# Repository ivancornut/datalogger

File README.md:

# Open Ecophysio Dataloggers
A competitive datalogger for use in environmental science. It is well adapted for work in remote locations with little access to networks. 

The big version of the datalogger is made to run on 12 or 24V lead batteries. This version has options to switch 12V or 5V loads.

The small version can run on 3 or 4 AA NiMh cells. It is made in a way that ensures very low consumption during sleep (few µAs). This gurantees around a year of logging before needing a battery change. 

Both versions have:
- a micro-SD card slot
- a very low-drift RTC for precise time-keeping
- battery voltage monitoring
- polarity and over-current protection

The interfacing software is compatible with windows, macOS and linux computers. It is made to be as simple to use as possible.

  * [Hardware](#hardware)
    + [Full size datalogger](#full-size-datalogger)
    + [Micro sized datalogger](#micro-sized-datalogger)
  * [Software](#software)
    + [On the computer](#on-the-computer)
    + [On the datalogger](#on-the-datalogger)

## Hardware
### Full size datalogger

We use a custom made PCB that integrates
- A battery input (usable with 12V lead batteries)
- a low consumption and high efficiency step-down converter that can convert 6-40V down to 5V
- a low-drift RTC clock
- An SD card slot
- two controllable power outputs of 5V and 12V (or battery voltage) using MOSFETs
- temperature corrected reference frequency generators from the RTC chip
- Qwiic compatible I2C and UART connectors
- A way to measure input battery voltage
### Micro sized datalogger

This is a miniaturized version of the big pcb when size is a constraint. It pushed all the power and clock circuitry beneath the Pi Pico.
It lacks some functionality of the bigger version such as the controllable power outputs and the full shutdown circuitry. 

## Software
### On the computer

We use two GUIs on the computer:
- one that generates the json configuration file for the datalogger
- one that enables communication with the datalogger to update the clock and download files from the SD card

The datalogger management GUI also allows you to setup the datalogger with all the necessary libraries and config files to start datalogging right away.
#### Windows installation of the management GUI
The graphical user interface to perform some interfacing functions was made to be as easy to use as possible. For windows an executable file was created by using the pyinstaller library. 

To run on windows you first need to install python on your computer. You can install it easily from the windows store.
Then open up the powershell:
```
pip install mpremote
```
That should do the trick and you can just run the full_management_gui.exe in the Software/computer folder. 
#### Linux machine
You just need to install the mpremote tool. 
```
pip install mpremote
```
And then go to the folder containing full_management_gui.py: 
```
python full_management_gui.py
```

### On the datalogger
We use two modules. The datalogger module and the sensor module.

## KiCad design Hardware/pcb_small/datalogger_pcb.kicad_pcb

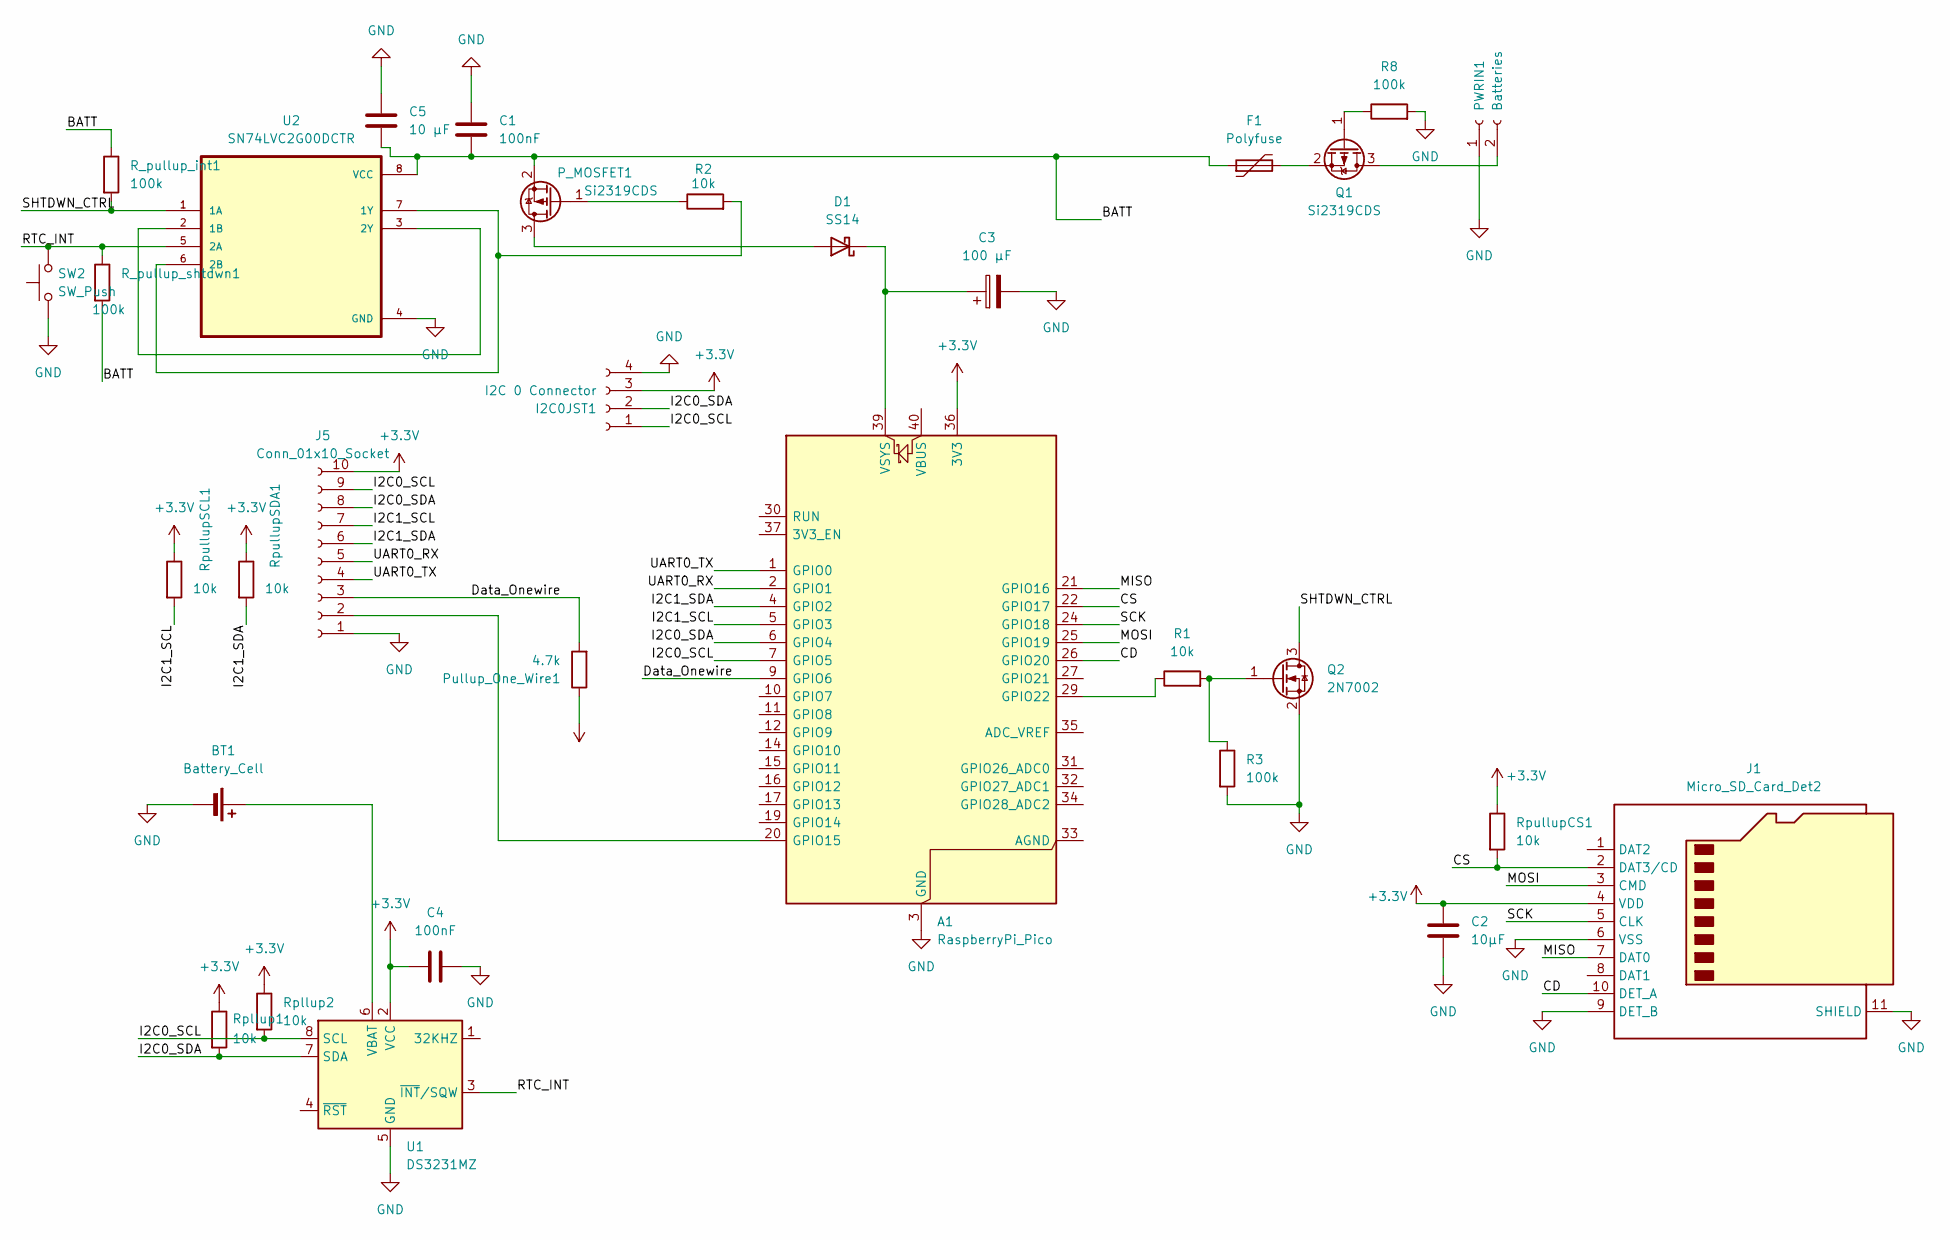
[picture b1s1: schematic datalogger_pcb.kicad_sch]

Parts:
A1: RaspberryPi_Pico; pi_pico_only_pins
BT1: Battery_Cell; BatteryHolder_Keystone_500
C1, C4: 100nF; C_1206_3216Metric_Pad1.33x1.80mm_HandSolder
C2: 10µF; C_1812_4532Metric_Pad1.57x3.40mm_HandSolder
C3: 100 µF; CP_Radial_D7.5mm_P2.50mm
C5: 10 µF; C_1812_4532Metric_Pad1.57x3.40mm_HandSolder
D1: SS14; D_SMA
F1: Polyfuse; R_Axial_DIN0207_L6.3mm_D2.5mm_P5.08mm_Vertical
I2C0JST1: I2C 0 Connector; PinSocket_1x04_P2.00mm_Vertical
J1: Micro_SD_Card_Det2; microSD_HC_Molex_104031-0811
J5: Conn_01x10_Socket; TerminalBlock_Phoenix_MKDS-1-10-3.81_1x10_P3.81mm_Horizontal
PWRIN1: Batteries; TerminalBlock_Phoenix_MKDS-1,5-2-5.08_1x02_P5.08mm_Horizont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
P_MOSFET1: Si2319CDS; SOT-23
Pullup_One_Wire1: 4.7k; R_Axial_DIN0204_L3.6mm_D1.6mm_P5.08mm_Vertical
Q1: Si2319CDS; SOT-23
Q2: 2N7002; SOT-23
R1, R2: 10k; R_0805_2012Metric_Pad1.20x1.40mm_HandSolder
R3, R8: 100k; R_0805_2012Metric_Pad1.20x1.40mm_HandSolder
R_pullup_int1: 100k; R_0805_2012Metric_Pad1.20x1.40mm_HandSolder
R_pullup_shtdwn1: 100k; R_0805_2012Metric_Pad1.20x1.40mm_HandSolder
Rpllup1, Rpllup2: 10k; R_0805_2012Metric_Pad1.20x1.40mm_HandSolder
RpullupCS1: 10k; R_0805_2012Metric_Pad1.20x1.40mm_HandSolder
RpullupSCL1: 10k; R_Axial_DIN0204_L3.6mm_D1.6mm_P5.08mm_Vertical
RpullupSDA1: 10k; R_Axial_DIN0204_L3.6mm_D1.6mm_P5.08mm_Vertical
SW2: SW_Push; SW_PUSH_6mm_H4.3mm
U1: DS3231MZ; SOIC-8_3.9x4.9mm_P1.27mm
U2: SN74LVC2G00DCTR; SSOP-8_2.95x2.8mm_P0.65mm - SN74LVC2G00

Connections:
+3.3V: A1.36 (3V3), C2.1, C4.1, I2C0JST1.3, J1.4 (VDD), J5.10, Pullup_One_Wire1.1, Rpllup1.1, Rpllup2.1, RpullupCS1.1, RpullupSCL1.1, RpullupSDA1.1, U1.2 (VCC)
/BATT: C1.1, C5.1, F1.1, P_MOSFET1.2 (S), R_pullup_int1.1, R_pullup_shtdwn1.2, U2.8 (VCC)
/CD: A1.26 (GPIO20), J1.10 (DET_A)
/CS: A1.22 (GPIO17), J1.2 (DAT3/CD), RpullupCS1.2
/Data_Onewire: A1.9 (GPIO6), J5.3, Pullup_One_Wire1.2
/I2C0_SCL: A1.7 (GPIO5), I2C0JST1.1, J5.9, Rpllup2.2, U1.8 (SCL)
/I2C0_SDA: A1.6 (GPIO4), I2C0JST1.2, J5.8, Rpllup1.2, U1.7 (SDA)
/I2C1_SCL: A1.5 (GPIO3), J5.7, RpullupSCL1.2
/I2C1_SDA: A1.4 (GPIO2), J5.6, RpullupSDA1.2
/MISO: A1.21 (GPIO16), J1.7 (DAT0)
/MOSI: A1.25 (GPIO19), J1.3 (CMD)
/RTC_INT: R_pullup_shtdwn1.1, SW2.2, U1.3 (~INT/SQW), U2.5 (2A)
/SCK: A1.24 (GPIO18), J1.5 (CLK)
/SHTDWN_CTRL: Q2.3 (D), R_pullup_int1.2, U2.1 (1A)
/UART0_RX: A1.2 (GPIO1), J5.5
/UART0_TX: A1.1 (GPIO0), J5.4
GND: A1.3 (GND), A1.8 (GND), A1.13 (GND), A1.18 (GND), A1.23 (GND), A1.28 (GND), A1.38 (GND), BT1.2 (-), C1.2, C2.2, C3.2, C4.2, C5.2, I2C0JST1.4, J1.6 (VSS), J1.9 (DET_B), J1.11 (SHIELD), J5.1, PWRIN1.1, Q2.2 (S), R3.2, R8.2, SW2.1, U1.5 (GND), U2.4 (GND)
unnamed: A1.20 (GPIO15), J5.2
unnamed: A1.29 (GPIO22), R1.1
unnamed: A1.39 (VSYS), C3.1, D1.1 (K)
unnamed: BT1.1 (+), U1.6 (VBAT)
unnamed: D1.2 (A), P_MOSFET1.3 (D)
unnamed: PWRIN1.2, Q1.3 (D)
unnamed: P_MOSFET1.1 (G), R2.1
unnamed: Q1.1 (G), R8.1
unnamed: F1.2, Q1.2 (S)
unnamed: Q2.1 (G), R1.2, R3.1
unnamed: U2.2 (1B), U2.3 (2Y)
unnamed: R2.2, U2.6 (2B), U2.7 (1Y)

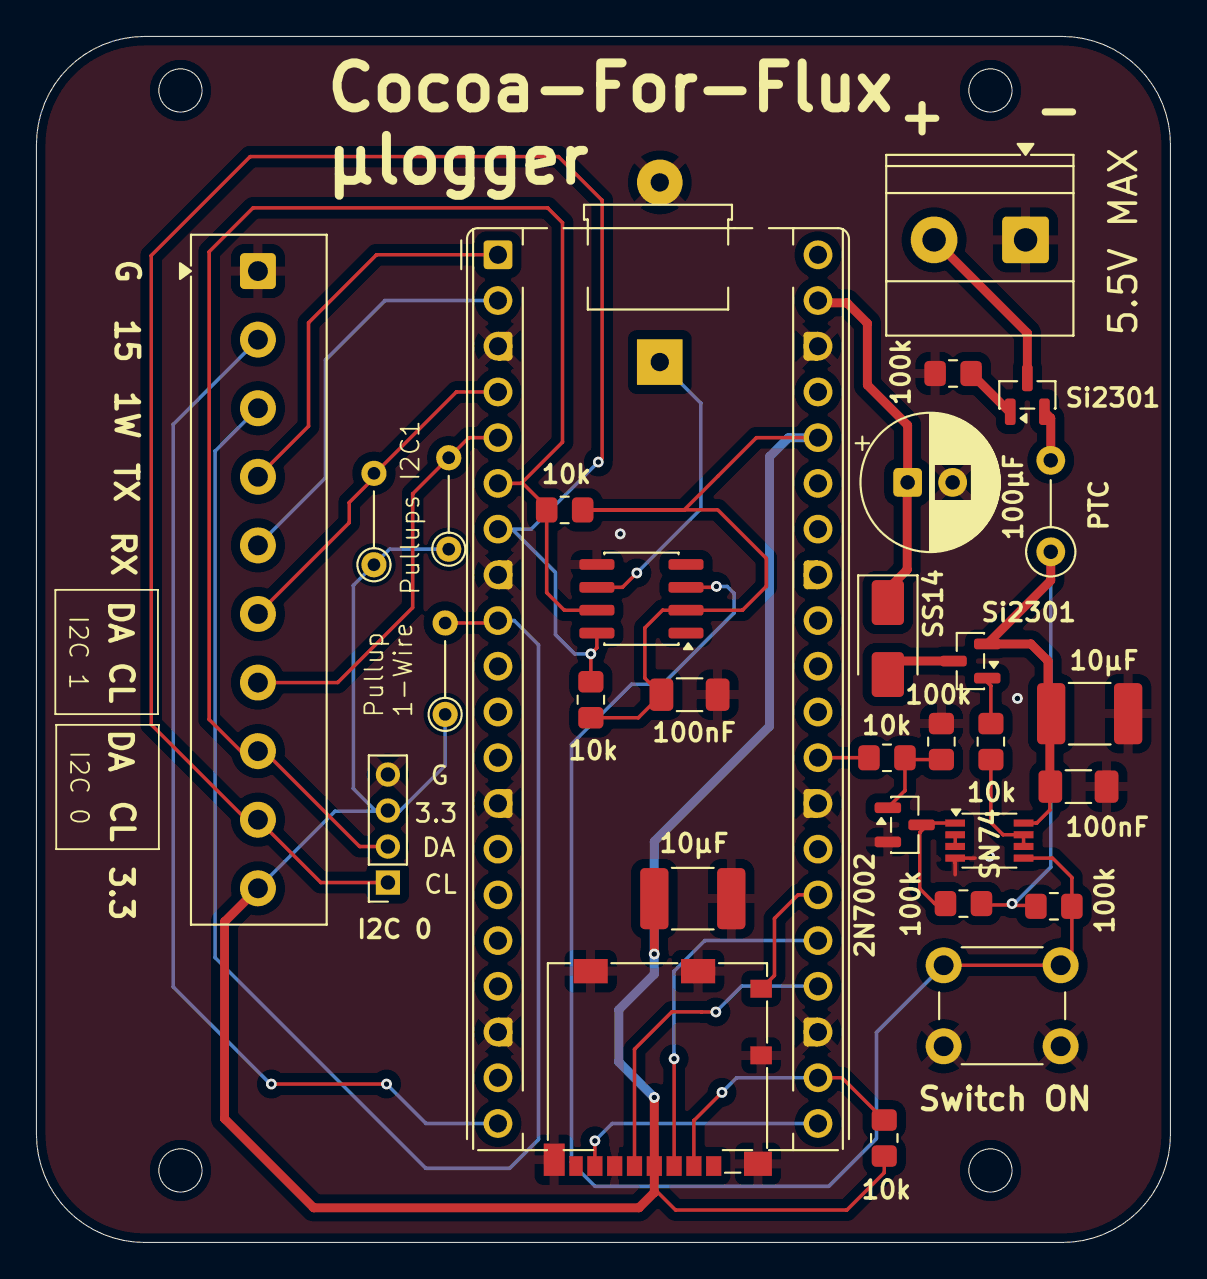
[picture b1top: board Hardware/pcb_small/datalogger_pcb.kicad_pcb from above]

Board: 2 copper layers, 63.0 x 67.0 mm, 31 parts (1 on the bottom side), 29 nets.

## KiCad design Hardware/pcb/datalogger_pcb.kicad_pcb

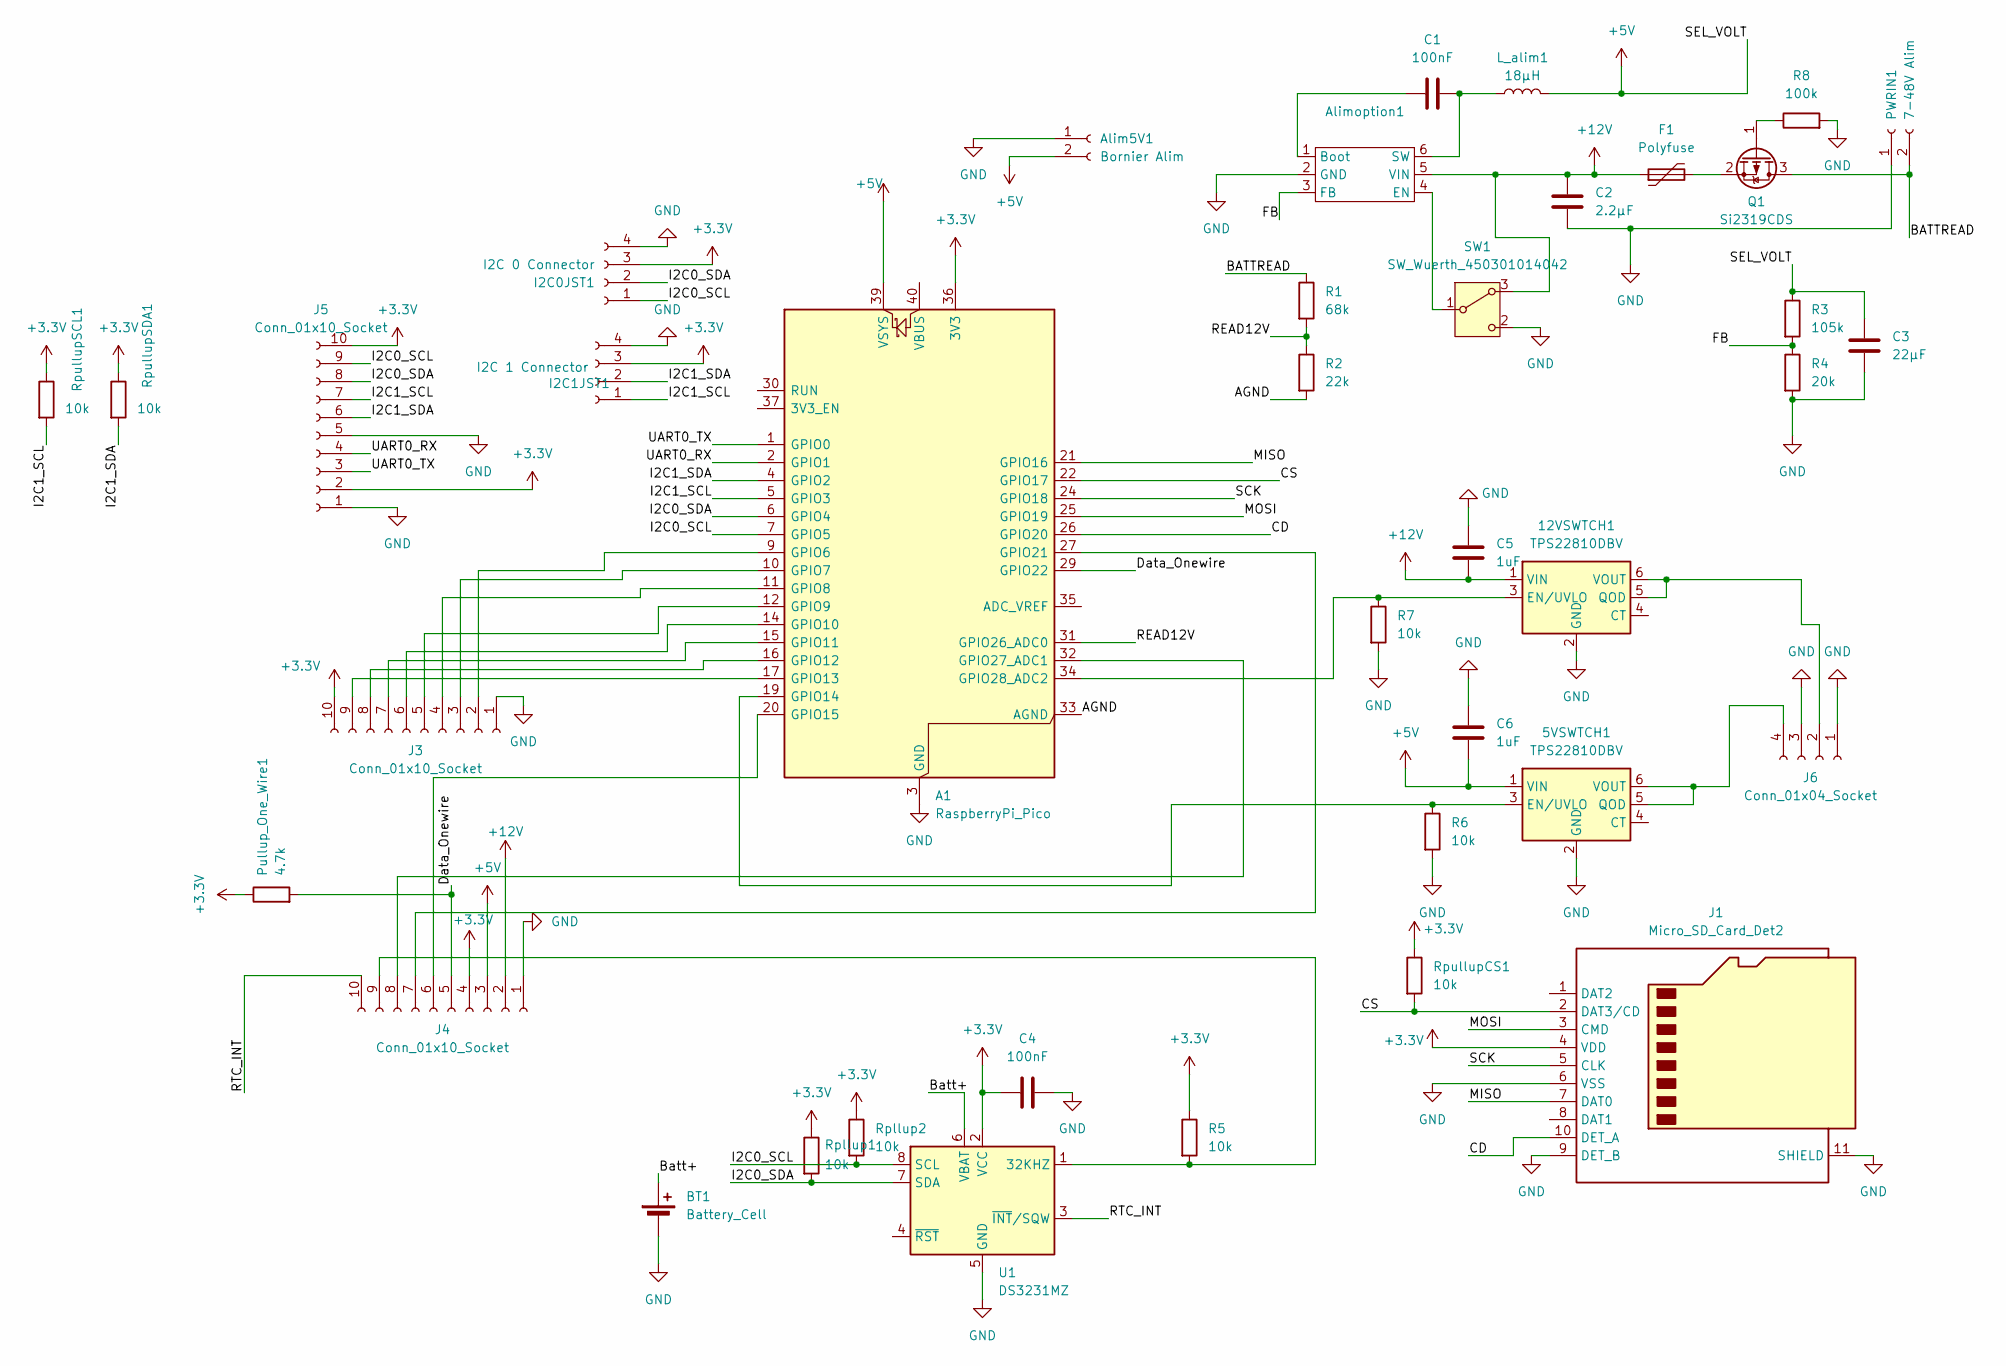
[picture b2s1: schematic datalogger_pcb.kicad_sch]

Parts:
5VSWTCH1, 12VSWTCH1: TPS22810DBV; SOT-23-6
A1: RaspberryPi_Pico; pi_pico_only_pins
Alim5V1: Bornier Alim; TerminalBlock_Phoenix_MKDS-1,5-2-5.08_1x02_P5.08mm_Horizont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
Alimoption1: TSOT-23-6_NEX
BT1: Battery_Cell; BatteryHolder_Keystone_500
C1, C4: 100nF; C_1812_4532Metric_Pad1.57x3.40mm_HandSolder
C2: 2.2µF; C_1812_4532Metric_Pad1.57x3.40mm_HandSolder
C3: 22µF; C_1812_4532Metric_Pad1.57x3.40mm_HandSolder
C5, C6: 1uF; C_1812_4532Metric_Pad1.57x3.40mm_HandSolder
F1: Polyfuse; R_Axial_DIN0207_L6.3mm_D2.5mm_P5.08mm_Vertical
I2C0JST1: I2C 0 Connector; PinSocket_1x04_P2.00mm_Vertical
I2C1JST1: I2C 1 Connector; PinSocket_1x04_P2.00mm_Vertical
J1: Micro_SD_Card_Det2; microSD_HC_Molex_104031-0811
J3, J4, J5: Conn_01x10_Socket; TerminalBlock_Phoenix_MKDS-1-10-3.81_1x10_P3.81mm_Horizontal
J6: Conn_01x04_Socket; TerminalBlock_Phoenix_MKDS-1,5-4-5.08_1x04_P5.08mm_Horizont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
L_alim1: 18µH; L_TracoPower_TCK-047_5.2x5.8mm
PWRIN1: 7-48V Alim; TerminalBlock_Phoenix_MKDS-1,5-2-5.08_1x02_P5.08mm_Horizont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
Pullup_One_Wire1: 4.7k; R_Axial_DIN0204_L3.6mm_D1.6mm_P5.08mm_Vertical
Q1: Si2319CDS; SOT-23
R1: 68k; R_0805_2012Metric_Pad1.20x1.40mm_HandSolder
R2: 22k; R_0805_2012Metric_Pad1.20x1.40mm_HandSolder
R3: 105k; R_0805_2012Metric_Pad1.20x1.40mm_HandSolder
R4: 20k; R_0805_2012Metric_Pad1.20x1.40mm_HandSolder
R5, R6, R7: 10k; R_0805_2012Metric_Pad1.20x1.40mm_HandSolder
R8: 100k; R_0805_2012Metric_Pad1.20x1.40mm_HandSolder
Rpllup1, Rpllup2: 10k; R_0805_2012Metric_Pad1.20x1.40mm_HandSolder
RpullupCS1: 10k; R_0805_2012Metric_Pad1.20x1.40mm_HandSolder
RpullupSCL1: 10k; R_Axial_DIN0204_L3.6mm_D1.6mm_P5.08mm_Vertical
RpullupSDA1: 10k; R_Axial_DIN0204_L3.6mm_D1.6mm_P5.08mm_Vertical
SW1: SW_Wuerth_450301014042; SW_Slide-03_Wuerth-WS-SLTV_10x2.5x6.4_P2.54mm
U1: DS3231MZ; SOIC-8_3.9x4.9mm_P1.27mm

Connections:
+3.3V: A1.36 (3V3), C4.1, I2C0JST1.3, I2C1JST1.3, J1.4 (VDD), J3.10, J4.4, J5.2, J5.10, Pullup_One_Wire1.1, R5.1, Rpllup1.1, Rpllup2.1, RpullupCS1.1, RpullupSCL1.1, RpullupSDA1.1, U1.2 (VCC)
+5V: 5VSWTCH1.1 (VIN), A1.39 (VSYS), Alim5V1.2, C3.1, C6.2, J4.3, L_alim1.2, R3.1
+12V: 12VSWTCH1.1 (VIN), Alimoption1.5 (VIN), C2.1, C5.2, F1.1, J4.2, SW1.3 (A)
/AGND: A1.33 (AGND), R2.2
/BATTREAD: PWRIN1.2, Q1.3 (D), R1.1
/Batt+: BT1.1 (+), U1.6 (VBAT)
/CD: A1.26 (GPIO20), J1.10 (DET_A)
/CS: A1.22 (GPIO17), J1.2 (DAT3/CD), RpullupCS1.2
/Data_Onewire: A1.29 (GPIO22), J4.5, Pullup_One_Wire1.2
/FB: Alimoption1.3 (FB), R3.2, R4.1
/I2C0_SCL: A1.7 (GPIO5), I2C0JST1.1, J5.9, Rpllup2.2, U1.8 (SCL)
/I2C0_SDA: A1.6 (GPIO4), I2C0JST1.2, J5.8, Rpllup1.2, U1.7 (SDA)
/I2C1_SCL: A1.5 (GPIO3), I2C1JST1.1, J5.7, RpullupSCL1.2
/I2C1_SDA: A1.4 (GPIO2), I2C1JST1.2, J5.6, RpullupSDA1.2
/MISO: A1.21 (GPIO16), J1.7 (DAT0)
/MOSI: A1.25 (GPIO19), J1.3 (CMD)
/READ12V: A1.31 (GPIO26_ADC0), R1.2, R2.1
/RTC_INT: J4.10, U1.3 (~INT/SQW)
/SCK: A1.24 (GPIO18), J1.5 (CLK)
/UART0_RX: A1.2 (GPIO1), J5.4
/UART0_TX: A1.1 (GPIO0), J5.3
GND: 5VSWTCH1.2 (GND), 12VSWTCH1.2 (GND), A1.3 (GND), A1.8 (GND), A1.13 (GND), A1.18 (GND), A1.23 (GND), A1.28 (GND), A1.38 (GND), Alim5V1.1, Alimoption1.2 (GND), BT1.2 (-), C2.2, C3.2, C4.2, C5.1, C6.1, I2C0JST1.4, I2C1JST1.4, J1.6 (VSS), J1.9 (DET_B), J1.11 (SHIELD), J3.1, J4.1, J5.1, J5.5, J6.1, J6.3, PWRIN1.1, R4.2, R6.2, R7.2, R8.2, SW1.2 (C), U1.5 (GND)
unnamed: 5VSWTCH1.3 (EN/UVLO), A1.19 (GPIO14), R6.1
unnamed: 5VSWTCH1.5 (QOD), 5VSWTCH1.6 (VOUT), J6.4
unnamed: 12VSWTCH1.3 (EN/UVLO), A1.34 (GPIO28_ADC2), R7.1
unnamed: 12VSWTCH1.5 (QOD), 12VSWTCH1.6 (VOUT), J6.2
unnamed: A1.9 (GPIO6), J3.2
unnamed: A1.10 (GPIO7), J3.3
unnamed: A1.11 (GPIO8), J3.4
unnamed: A1.12 (GPIO9), J3.5
unnamed: A1.14 (GPIO10), J3.6
unnamed: A1.15 (GPIO11), J3.7
unnamed: A1.16 (GPIO12), J3.8
unnamed: A1.17 (GPIO13), J3.9
unnamed: A1.20 (GPIO15), J4.6
unnamed: A1.27 (GPIO21), J4.7
unnamed: A1.32 (GPIO27_ADC1), J4.8
unnamed: Alimoption1.1 (Boot), C1.1
unnamed: Alimoption1.4 (EN), SW1.1 (B)
unnamed: Alimoption1.6 (SW), C1.2, L_alim1.1
unnamed: J4.9, R5.2, U1.1 (32KHZ)
unnamed: Q1.1 (G), R8.1
unnamed: F1.2, Q1.2 (S)

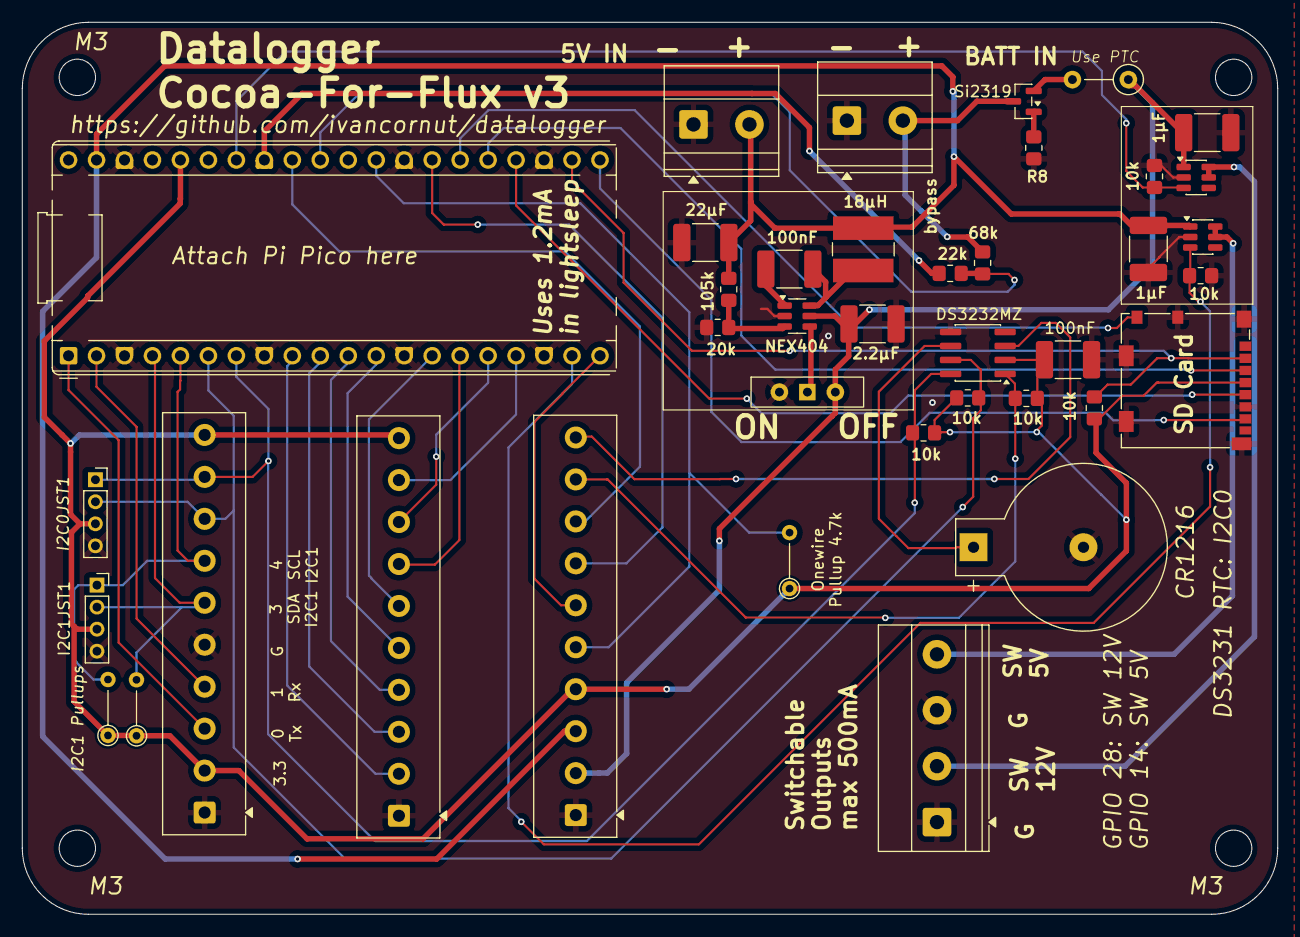
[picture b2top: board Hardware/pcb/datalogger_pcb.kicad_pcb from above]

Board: 2 copper layers, 114.0 x 81.0 mm, 39 parts (0 on the bottom side), 43 nets.

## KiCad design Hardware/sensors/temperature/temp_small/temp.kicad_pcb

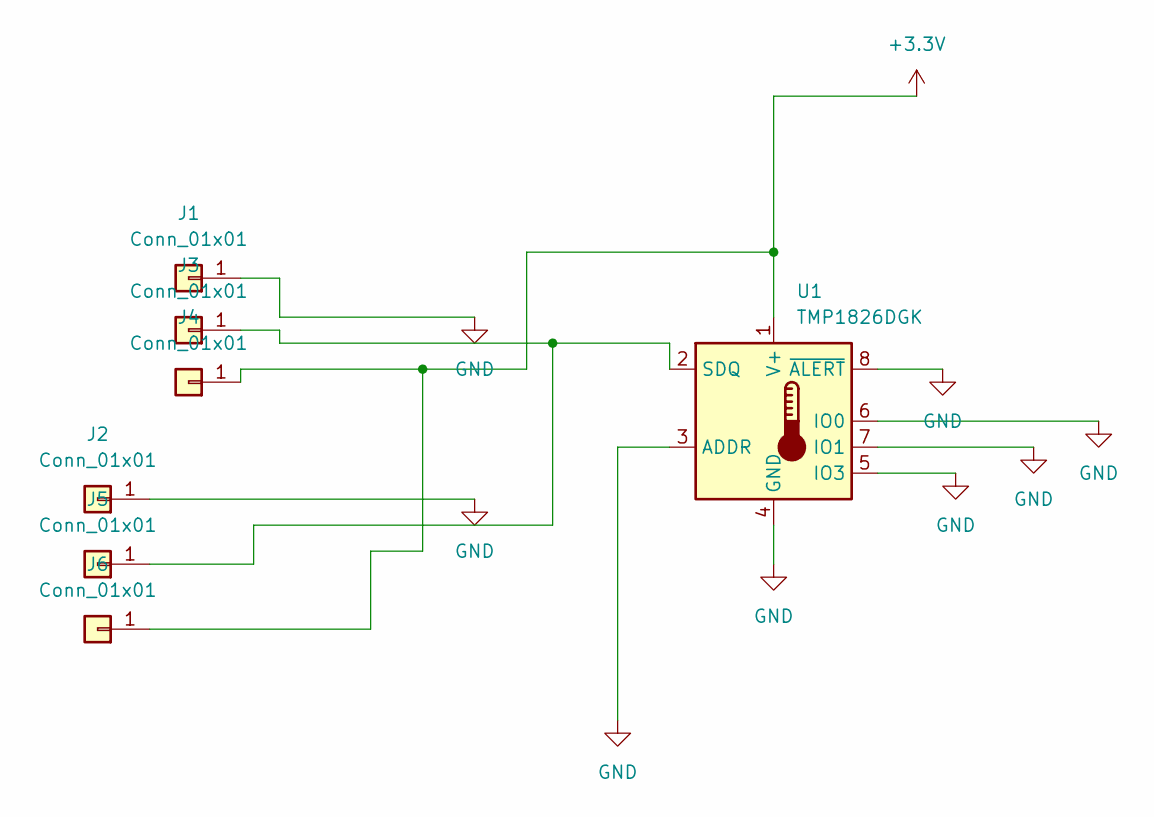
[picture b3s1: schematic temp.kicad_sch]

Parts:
J1, J2, J3, J4, J5, J6: Conn_01x01; PinHeader_1x01_P1.27mm_Vertical
U1: TMP1826DGK; VSSOP-8_3x3mm_P0.65mm

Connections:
+3.3V: J4.1, J6.1, U1.1 (V+)
GND: J1.1, J2.1, U1.3 (ADDR), U1.4 (GND), U1.5 (IO3), U1.6 (IO0), U1.7 (IO1), U1.8 (~ALERT)
unnamed: J3.1, J5.1, U1.2 (SDQ)

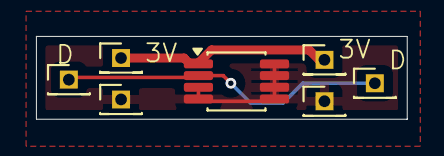
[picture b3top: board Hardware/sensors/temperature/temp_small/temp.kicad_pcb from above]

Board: 2 copper layers, 20.6 x 4.6 mm, 7 parts (0 on the bottom side), 3 nets.

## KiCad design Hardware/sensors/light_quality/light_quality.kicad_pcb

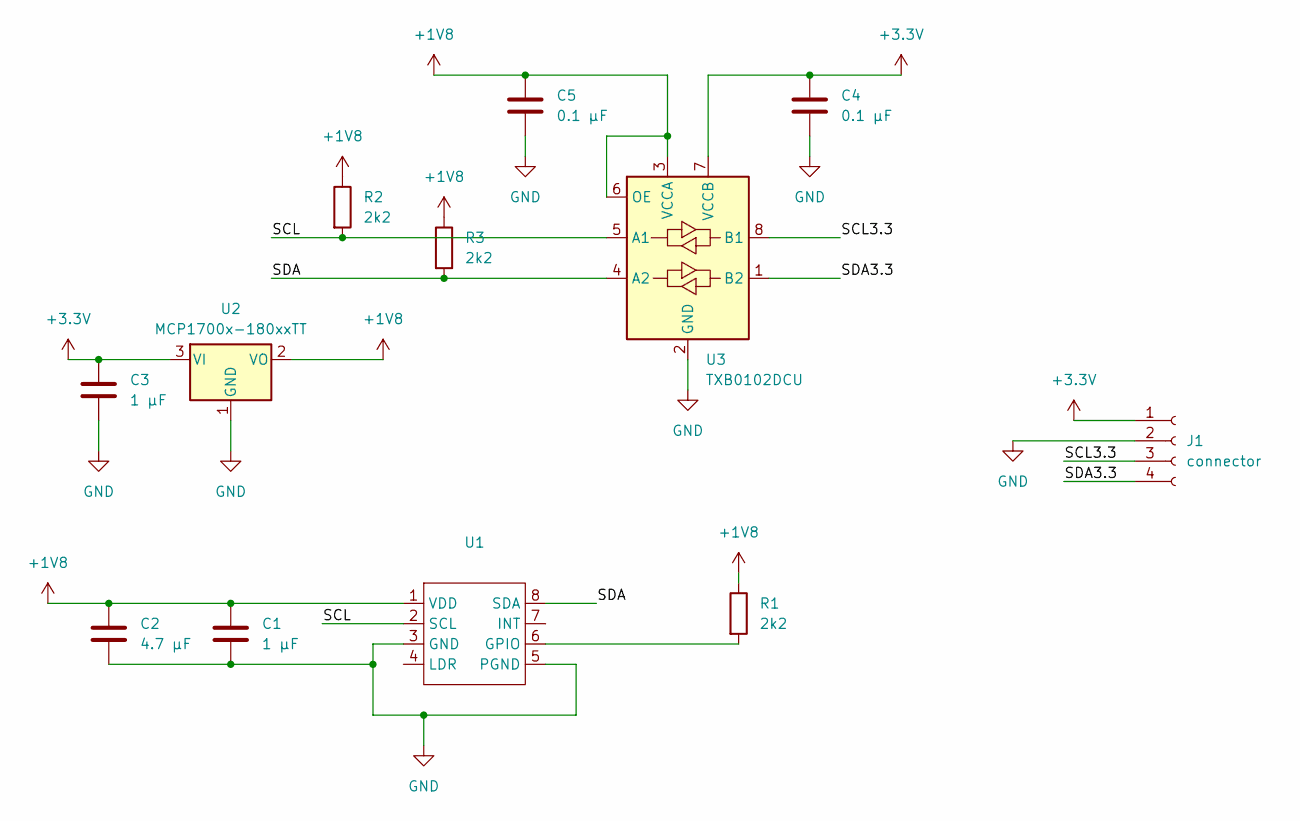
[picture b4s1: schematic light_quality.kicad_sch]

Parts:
C1, C3: 1 µF; C_0805_2012Metric_Pad1.18x1.45mm_HandSolder
C2: 4.7 µF; C_0805_2012Metric_Pad1.18x1.45mm_HandSolder
C4, C5: 0.1 µF; C_0805_2012Metric_Pad1.18x1.45mm_HandSolder
J1: connector; PinSocket_1x04_P2.00mm_Vertical
R1, R2, R3: 2k2; R_0805_2012Metric_Pad1.20x1.40mm_HandSolder
U1: AMS_OLGA-8_2x3.1mm_P0.8mm
U2: MCP1700x-180xxTT; SOT-23
U3: TXB0102DCU; VSSOP-8_2.3x2mm_P0.5mm

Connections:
+1V8: C1.1, C2.1, C5.1, R1.1, R2.1, R3.1, U1.1 (VDD), U2.2 (VO), U3.3 (VCCA), U3.6 (OE)
+3.3V: C3.1, C4.1, J1.1, U2.3 (VI), U3.7 (VCCB)
/SCL: R2.2, U1.2 (SCL), U3.5 (A1)
/SCL3.3: J1.3, U3.8 (B1)
/SDA: R3.2, U1.8 (SDA), U3.4 (A2)
/SDA3.3: J1.4, U3.1 (B2)
GND: C1.2, C2.2, C3.2, C4.2, C5.2, J1.2, U1.3 (GND), U1.5 (PGND), U2.1 (GND), U3.2 (GND)
unnamed: R1.2, U1.6 (GPIO)

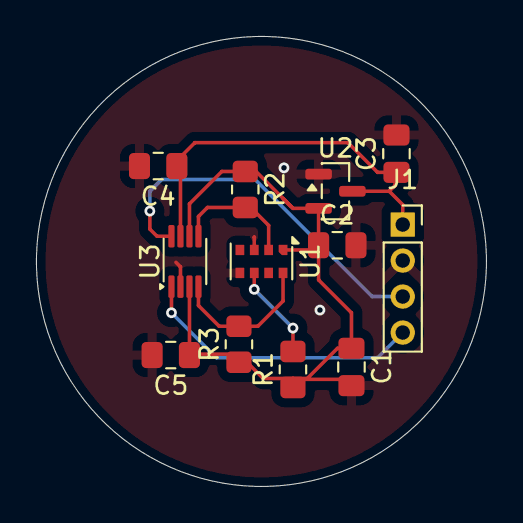
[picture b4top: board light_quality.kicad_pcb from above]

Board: 2 copper layers, 25.0 x 25.0 mm, 12 parts (0 on the bottom side), 8 nets.

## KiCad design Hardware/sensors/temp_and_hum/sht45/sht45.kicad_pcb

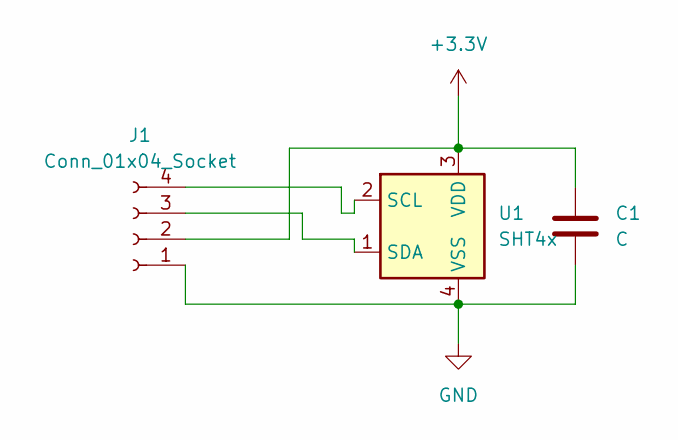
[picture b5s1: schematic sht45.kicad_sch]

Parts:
C1: C; C_0805_2012Metric_Pad1.18x1.45mm_HandSolder
J1: Conn_01x04_Socket; NS-Tech_Grove_1x04_P2mm_Vertical
U1: SHT4x; Sensirion_DFN-4_1.5x1.5mm_P0.8mm_SHT4x_NoCentralPad

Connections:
+3.3V: C1.1, J1.2, U1.3 (VDD)
GND: C1.2, J1.1, U1.4 (VSS)
unnamed: J1.3, U1.1 (SDA)
unnamed: J1.4, U1.2 (SCL)

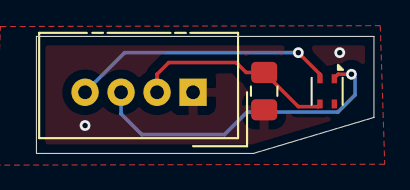
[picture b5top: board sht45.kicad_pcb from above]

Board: 2 copper layers, 18.8 x 6.5 mm, 3 parts (0 on the bottom side), 4 nets.

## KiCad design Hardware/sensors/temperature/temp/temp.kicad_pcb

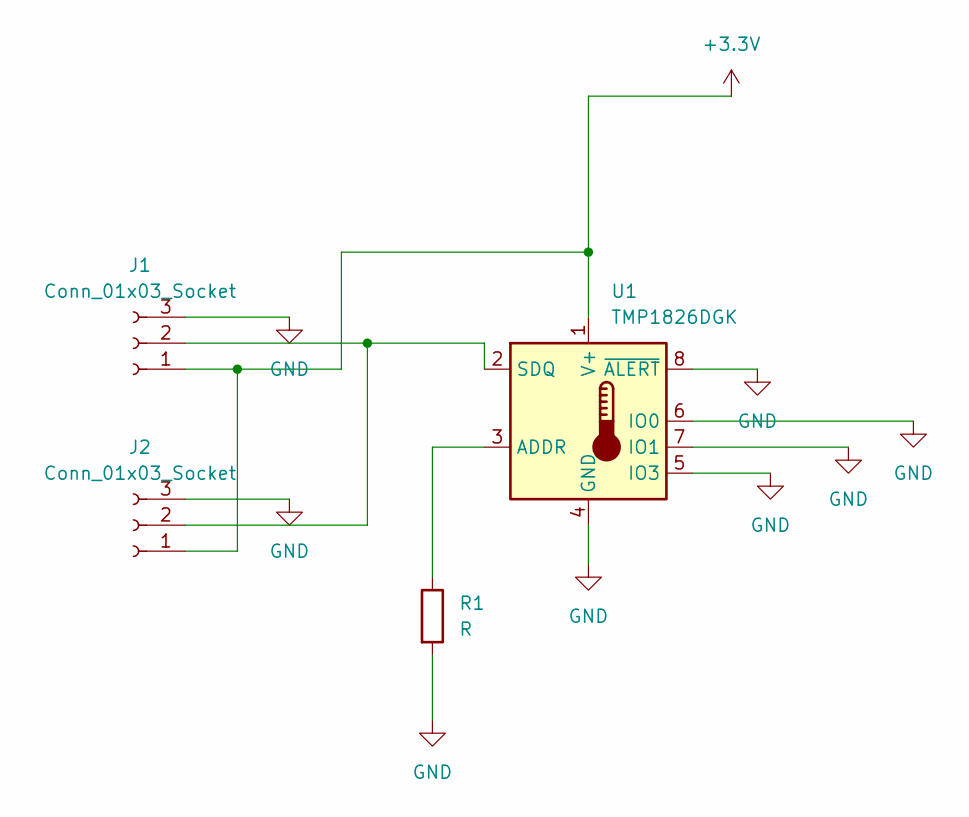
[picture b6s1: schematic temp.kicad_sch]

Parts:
J1, J2: Conn_01x03_Socket; PinSocket_1x03_P2.00mm_Vertical
R1: R; R_0805_2012Metric_Pad1.20x1.40mm_HandSolder
U1: TMP1826DGK; VSSOP-8_3x3mm_P0.65mm

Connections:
+3.3V: J1.1, J2.1, U1.1 (V+)
GND: J1.3, J2.3, R1.2, U1.4 (GND), U1.5 (IO3), U1.6 (IO0), U1.7 (IO1), U1.8 (~ALERT)
unnamed: J1.2, J2.2, U1.2 (SDQ)
unnamed: R1.1, U1.3 (ADDR)

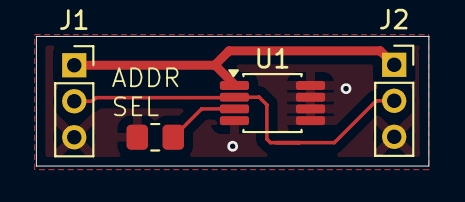
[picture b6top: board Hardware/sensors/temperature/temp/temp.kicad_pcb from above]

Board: 2 copper layers, 21.8 x 7.2 mm, 4 parts (0 on the bottom side), 4 nets.

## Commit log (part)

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2026-02-02 Added pcb files
2026-02-02 Added GUI interface for datalogger
2026-02-02 Added pcb image
2026-02-02 change picture of GUIs
2026-02-17 Made cs616 work with new pcbs and disable pin
2026-02-19 Created small version of pcb
2026-02-19 Finalised design for micrologger
2026-02-20 Corrected screw diameter error
2026-03-03 created windows executable
2026-03-03 Added small icon
2026-03-03 Adapted programm to work on windows
2026-03-03 added comments
2026-03-05 updated code
2026-03-05 Added the libraries that are necessary on the pico
2026-03-05 Made changes to the gui
2026-03-06 New code that contains everything
2026-03-06 made new executable
2026-03-06 Improved readability of interface
2026-03-06 small interface changes
2026-03-06 Small style changes
2026-03-06 changed image example of GUI
2026-03-14 Changes to filename management
2026-03-18 Added daily machine reset to code to prevent shutdowns
2026-03-18 Changed file download from sd card
2026-03-18 New executable
2026-04-20 Small changes in datalogger micropython
2026-04-22 Repaired critical bugs in micropython progs
2026-04-24 Changed way of resetting in datalogger manage
2026-04-26 Added temperature 1-wire pcb
2026-04-26 improved temperature 1-wire pcb
2026-04-27 Added latching shutdown
2026-04-27 Smaller temp pcb
2026-05-11 Added PAR sensor PCB
